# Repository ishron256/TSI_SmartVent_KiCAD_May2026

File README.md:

# TSI SmartVent — KiCAD Design Documents (May 2026)

This repository contains the KiCAD design documents for the **TSI SmartVent** project.  
All schematics, PCB layouts, libraries, and fabrication outputs are stored here and will be regularly updated.

---

## Repository Structure

```
TSI_SmartVent_KiCAD_May2026/
├── Schematic/       # KiCAD schematic files (.kicad_sch, .kicad_pro)
├── PCBLayout/       # KiCAD PCB layout files (.kicad_pcb)
├── Libraries/       # Custom symbol and footprint libraries
│   ├── Symbols/     # Custom schematic symbols (.kicad_sym)
│   └── Footprints/  # Custom PCB footprints (.pretty/)
└── Outputs/         # Fabrication outputs
    ├── Gerbers/     # Gerber files for PCB manufacturing
    ├── BOM/         # Bill of Materials
    └── PDF/         # PDF exports of schematics and layouts
```

---

## Getting Started

1. Install [KiCAD 8.x](https://www.kicad.org/download/) or later.
2. Clone this repository:
   ```bash
   git clone https://github.com/ishron256/TSI_SmartVent_KiCAD_May2026.git
   ```
3. Open the project file (`.kicad_pro`) in `Schematic/` with KiCAD.

---

## Contribution Guidelines

- Commit schematic and layout changes together where possible.
- Export updated Gerbers and BOM to `Outputs/` whenever a design revision is finalized.
- Use descriptive commit messages referencing the design revision (e.g., `Rev A – added power stage schematic`).
- Do **not** commit KiCAD auto-save or backup files (`*.kicad_sch-bak`, `_autosave-*`).

---

## License

© TSI — All rights reserved.

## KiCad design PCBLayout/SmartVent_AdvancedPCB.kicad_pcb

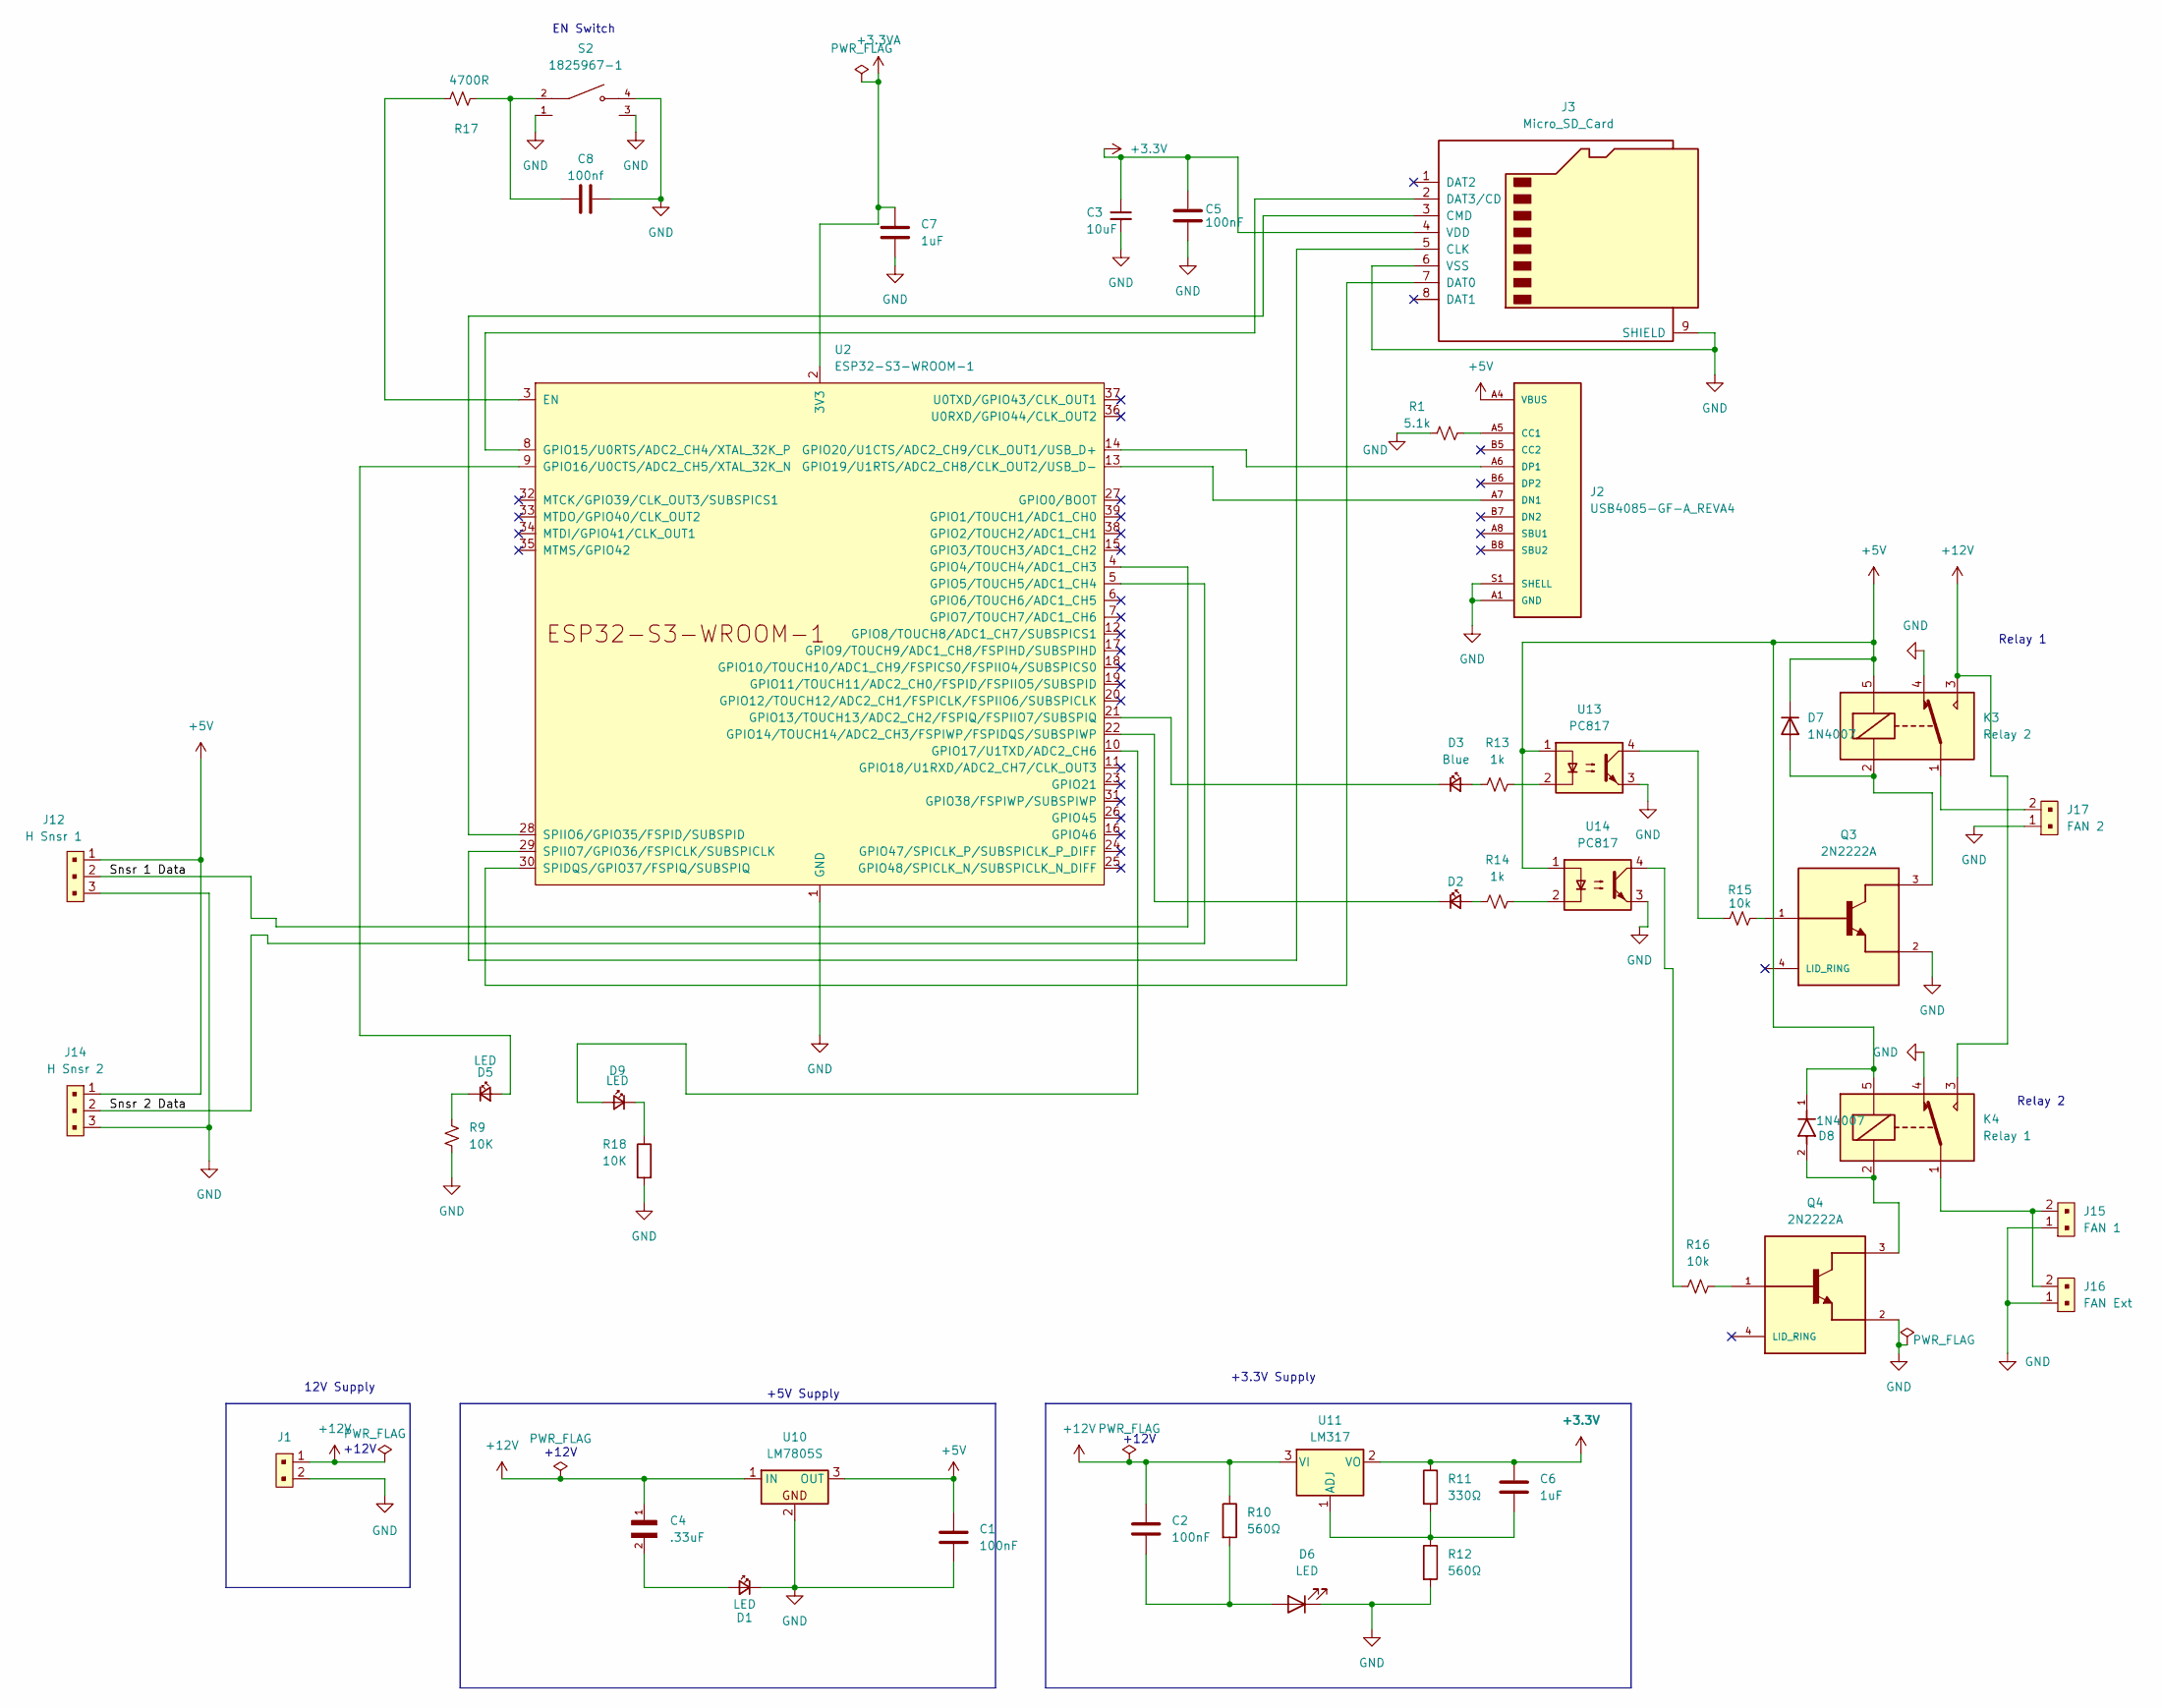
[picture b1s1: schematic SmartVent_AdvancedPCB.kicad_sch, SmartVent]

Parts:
C1, C2, C5: 100nF; SmartVent_Footprint_Capacitor_SMDC_0603_1608Metric_Kyocera_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
C3: 10uF; SmartVent_Footprints_C_0603_1608Metric_AVX_06033C103KAT2A; Voltage 6.3V; Tolerance 20%
C4: .33uF; SmartVent_Footprint_CAPC1608X90N_Kemet
C6, C7: 1uF; SmartVent_Footprint_C_0603_1608Metric_Yageo_CC0603MRX5R6BB1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
C8: 100nf; SmartVent_Footprint_Capacitor_SMDC_0603_1608Metric_Kyocera_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
D1, D6: LED; SmartVent_Footprint_LED_0603_1608Metric_Rohm_Green_SML-D12P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
D2, D3: Blue; SmartVent_Footprint_LED_0603_1608MetriRohm_Blue_SMLE12BC7TT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
D5, D9: LED; SmartVent_Footprint_LED_0603_1608Metric_Rohm_Red_SML-E12V8W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
D7: 1N4007; D_SOD-123F
D8: 1N4007; SmartVent_Footprint_D_SOD-123F_EIC_1n4007; PARTREV C
J1: 2 Pin Conn; JST_XH_B2B-XH-AM_1x02_P2.50mm_Vertical; MPN B2B-XH-A(LF)(SN); Digi-Key_PN 455-2247-ND
J2: USB4085-GF-A_REVA4; GCT_USB4085-GF-A_REVA4; PARTREV A4
J3: Micro_SD_Card; SmartVent_Footprint_microSD_HC_Wuerth_693072010801
J12: H Snsr 1; JST_XH_B3B-XH-A_1x03_P2.50mm_Vertical; MPN B3B-XH-A(LF)(SN); Digi-Key_PN 455-2248-ND
J14: H Snsr 2; JST_XH_B3B-XH-A_1x03_P2.50mm_Vertical; MPN B3B-XH-A(LF)(SN); Digi-Key_PN 455-2248-ND
J15: FAN 1; JST_XH_B2B-XH-A_1x02_P2.50mm_Vertical; MPN B2B-XH-A(LF)(SN); Digi-Key_PN 455-2247-ND
J16: FAN Ext; JST_XH_B2B-XH-A_1x02_P2.50mm_Vertical; MPN B2B-XH-A(LF)(SN); Digi-Key_PN 455-2247-ND
J17: FAN 2; JST_XH_B2B-XH-AM_1x02_P2.50mm_Vertical; MPN B2B-XH-A(LF)(SN); Digi-Key_PN 455-2247-ND
K3: Relay 2; SmartVent_Footprint_Relay_SPDT_SANYOU_SRD_Series_Form_C
K4: Relay 1; SmartVent_Footprint_Relay_SPDT_SANYOU_SRD_Series_Form_C
Q3, Q4: 2N2222A; SmartVent_Footprint_TRANS_2N2222AUBC; PARTREV 2
R1: 5.1k; R_0603_1608Metric
R9: 10K; R_0603_1608Metric_Pad0.98x0.95mm
R10, R12: 560Ω; R_0603_1608Metric_Pad0.98x0.95mm
R11: 330Ω; R_0603_1608Metric_Pad0.98x0.95mm
R13: 1k; R_0603_1608Metric
R14: 1k; SmartVent_Footprint_R_0201_0603Metric
R15, R16: 10k; R_0603_1608Metric_Pad0.98x0.95mm
R17: 4700R; R_0603_1608Metric_Pad0.98x0.95mm
R18: 10K; R_0603_1608Metric
S2: 1825967-1; SmartVent_Footprint_S2_SW_1825967-1; PARTREV E
U2: ESP32-S3-WROOM-1
U10: LM7805S; SmartVent_Footprint_U10_SOT-223-3_TabPin2; DigiKey_Part_Number 296-44520-1-ND
U11: LM317; SmartVent_Footprint_U11_SOT-223-3_TabPin2
U13, U14: PC817; SmartVent_Footprint_U13_U14_SOP254P975X460-4N

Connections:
+3.3V: C3.1, C5.1, C6.1, J3.4 (VDD), R11.1, U11.2 (VO)
+3.3VA: C7.1, U2.2 (3V3)
+5V: C1.1, D7.1 (K), D8.1, J2.A4 (VBUS), J2.A9 (VBUS), J2.B4 (VBUS), J2.B9 (VBUS), J12.1, J14.1, K3.5, K4.5, U10.3 (OUT), U13.1, U14.1
+12V: C2.1, C4.1, J1.1, K3.3, K4.3, R10.1, U10.1 (IN), U11.3 (VI)
/Snsr 1 Data: J12.2, U2.4 (GPIO4/TOUCH4/ADC1_CH3)
/Snsr 2 Data: J14.2, U2.5 (GPIO5/TOUCH5/ADC1_CH4)
GND: C1.2, C3.2, C5.2, C7.2, C8.1, D1.1 (K), D6.1 (K), J1.2, J2.A1 (GND), J2.A12 (GND), J2.B1 (GND), J2.B12 (GND), J2.S1 (SHELL), J2.S2 (SHELL), J2.S3 (SHELL), J2.S4 (SHELL), J3.6 (VSS), J3.9 (SHIELD), J12.3, J14.3, J15.1, J16.1, J17.1, K3.4, K4.4, Q3.2, Q4.2, R1.1, R9.2, R12.2, R18.2, S2.1, S2.3, S2.4, U2.1 (GND), U2.40 (GND), U2.41 (GND), U10.2, U13.3, U14.3
unnamed: C8.2, R17.1, S2.2
unnamed: C4.2, D1.2 (A)
unnamed: D2.2 (A), R14.2
unnamed: D2.1 (K), U2.22 (GPIO14/TOUCH14/ADC2_CH3/FSPIWP/FSPIDQS/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)
unnamed: D3.2 (A), R13.2
unnamed: D3.1 (K), U2.21 (GPIO13/TOUCH13/ADC2_CH2/FSPIQ/FSPIIO7/S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)
unnamed: D5.2 (A), U2.9 (GPIO16/U0CTS/ADC2_CH5/XTAL_32K_N)
unnamed: D5.1 (K), R9.1
unnamed: C2.2, D6.2 (A), R10.2
unnamed: D7.2 (A), K3.2, Q3.3
unnamed: D8.2, K4.2, Q4.3
unnamed: D9.2 (A), U2.10 (GPIO17/U1TXD/ADC2_CH6)
unnamed: D9.1 (K), R18.1
unnamed: J2.A5 (CC1), R1.2
unnamed: J2.A7 (DN1), U2.13 (GPIO19/U1RTS/ADC2_CH8/CLK_OUT2/USB_D-)
unnamed: J2.A6 (DP1), U2.14 (GPIO20/U1CTS/ADC2_CH9/CLK_OUT1/USB_D+)
unnamed: J3.5 (CLK), U2.29 (SPIIO7/GPIO36/FSPICLK/SUBSPICLK)
unnamed: J3.3 (CMD), U2.28 (SPIIO6/GPIO35/FSPID/SUBSPID)
unnamed: J3.7 (DAT0), U2.30 (SPIDQS/GPIO37/FSPIQ/SUBSPIQ)
unnamed: J3.2 (DAT3/CD), U2.8 (GPIO15/U0RTS/ADC2_CH4/XTAL_32K_P)
unnamed: J15.2, J16.2, K4.1
unnamed: J17.2, K3.1
unnamed: Q3.1, R15.1
unnamed: Q4.1, R16.1
unnamed: R13.1, U13.2
unnamed: R14.1, U14.2
unnamed: R15.2, U13.4
unnamed: R16.2, U14.4
unnamed: R17.2, U2.3 (EN)
unnamed: C6.2, R11.2, R12.1, U11.1 (ADJ)

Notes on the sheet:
12V Supply
Relay 2
EN Switch
Relay 1
+12V
+5V Supply
+12V
+3.3V Supply

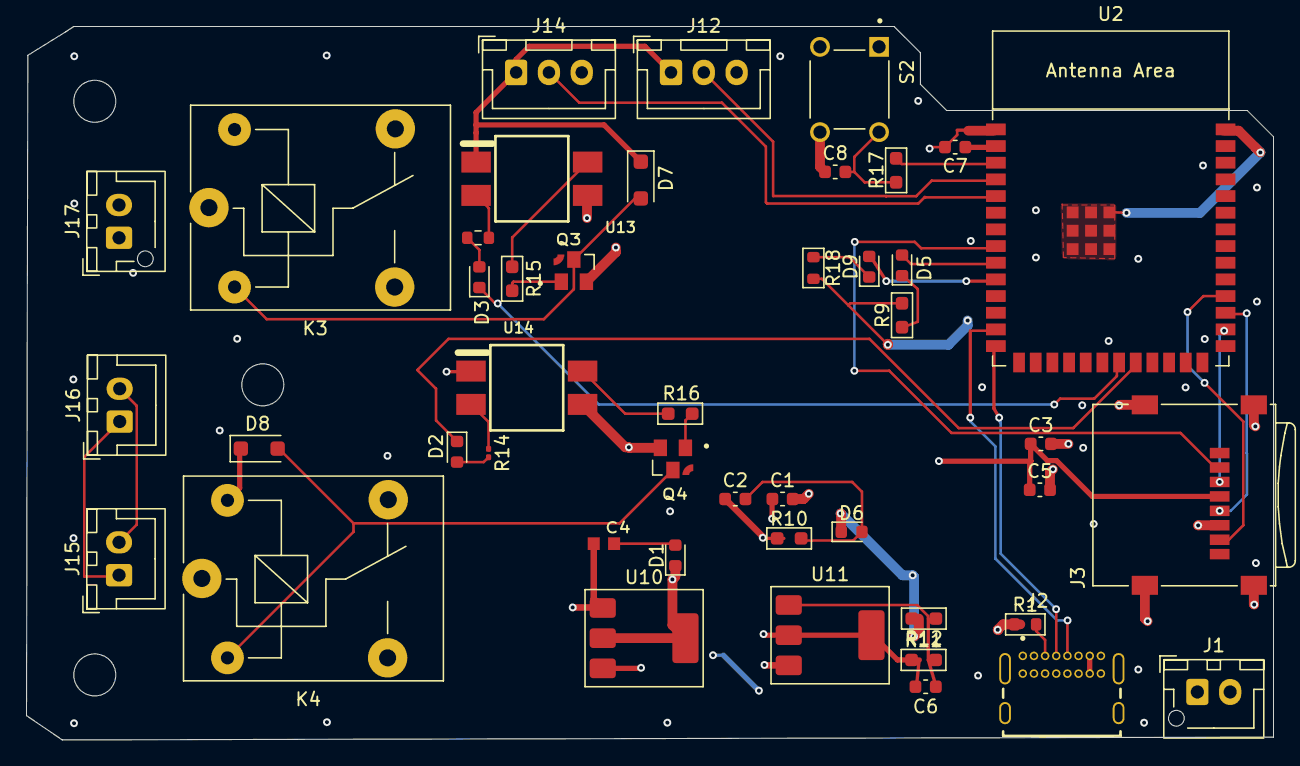
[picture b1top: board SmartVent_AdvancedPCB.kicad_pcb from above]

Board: 4 copper layers, 95.0 x 54.4 mm, 45 parts (0 on the bottom side), 37 nets.

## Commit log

2026-04-30 Initial plan
2026-04-30 Set up KiCAD project structure: README, .gitignore, and directory scaffold
    Agent-Logs-Url: https://github.com/ishron256/TSI_SmartVent_KiCAD_May2026/sessions/a3ef05f6-81e2-4876-b4a5-14bccbbf3feb
2026-04-30 New Version Control Enabled
    Initial Commit of the project files that I have been working on.
2026-04-30 Remove KiCAD lock file and add ~*.lck to .gitignore
    Agent-Logs-Url: https://github.com/ishron256/TSI_SmartVent_KiCAD_May2026/sessions/117bfb81-387c-4ee3-8a19-90cae8b7fe08
